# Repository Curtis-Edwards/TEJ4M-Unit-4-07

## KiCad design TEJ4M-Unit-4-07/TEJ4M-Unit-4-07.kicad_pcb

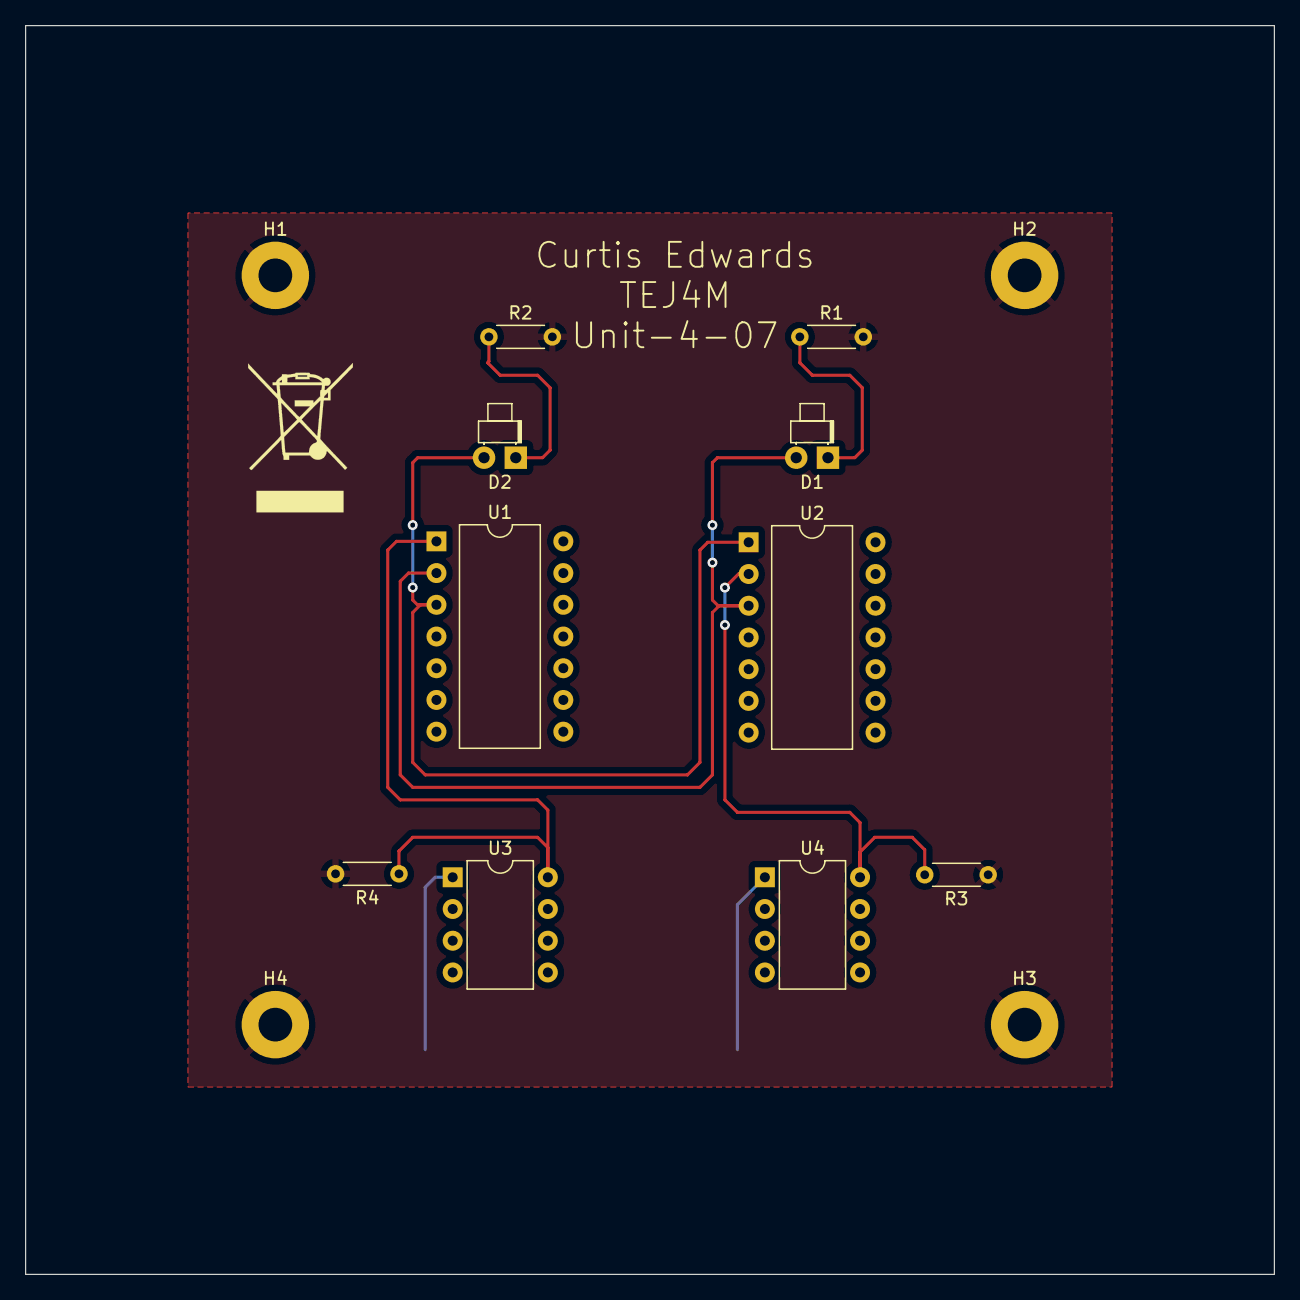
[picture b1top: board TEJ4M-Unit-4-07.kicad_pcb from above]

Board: 2 copper layers, 100.0 x 100.0 mm, 14 parts (0 on the bottom side), 8 nets.

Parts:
D1, D2: LED; LED_D1.8mm_W1.8mm_H2.4mm_Horizontal_O1.27mm_Z1.6mm
H1, H2, H3, H4: MountingHole_Pad; MountingHole_2.7mm_Pad
R1, R2, R3, R4: R_US; R_Axial_DIN0204_L3.6mm_D1.6mm_P5.08mm_Horizontal
U1, U2: 4001; DIP-14_W10.16mm
U3, U4: ADG417BN; DIP-8_W7.62mm

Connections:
+5V: U3.1, U4.1
GND: H1.1, H2.1, H3.1, H4.1, R1.2, R2.2, R3.1, R4.2
unnamed: D1.2 (A), U1.2, U2.3
unnamed: D1.1 (K), R1.1
unnamed: D2.2 (A), U1.3, U2.1
unnamed: D2.1 (K), R2.1
unnamed: R3.2, U2.2, U4.8
unnamed: R4.1, U1.1, U3.8
